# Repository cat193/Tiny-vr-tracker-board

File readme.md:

Mcu pcb is designed

IMU board is not finished yet

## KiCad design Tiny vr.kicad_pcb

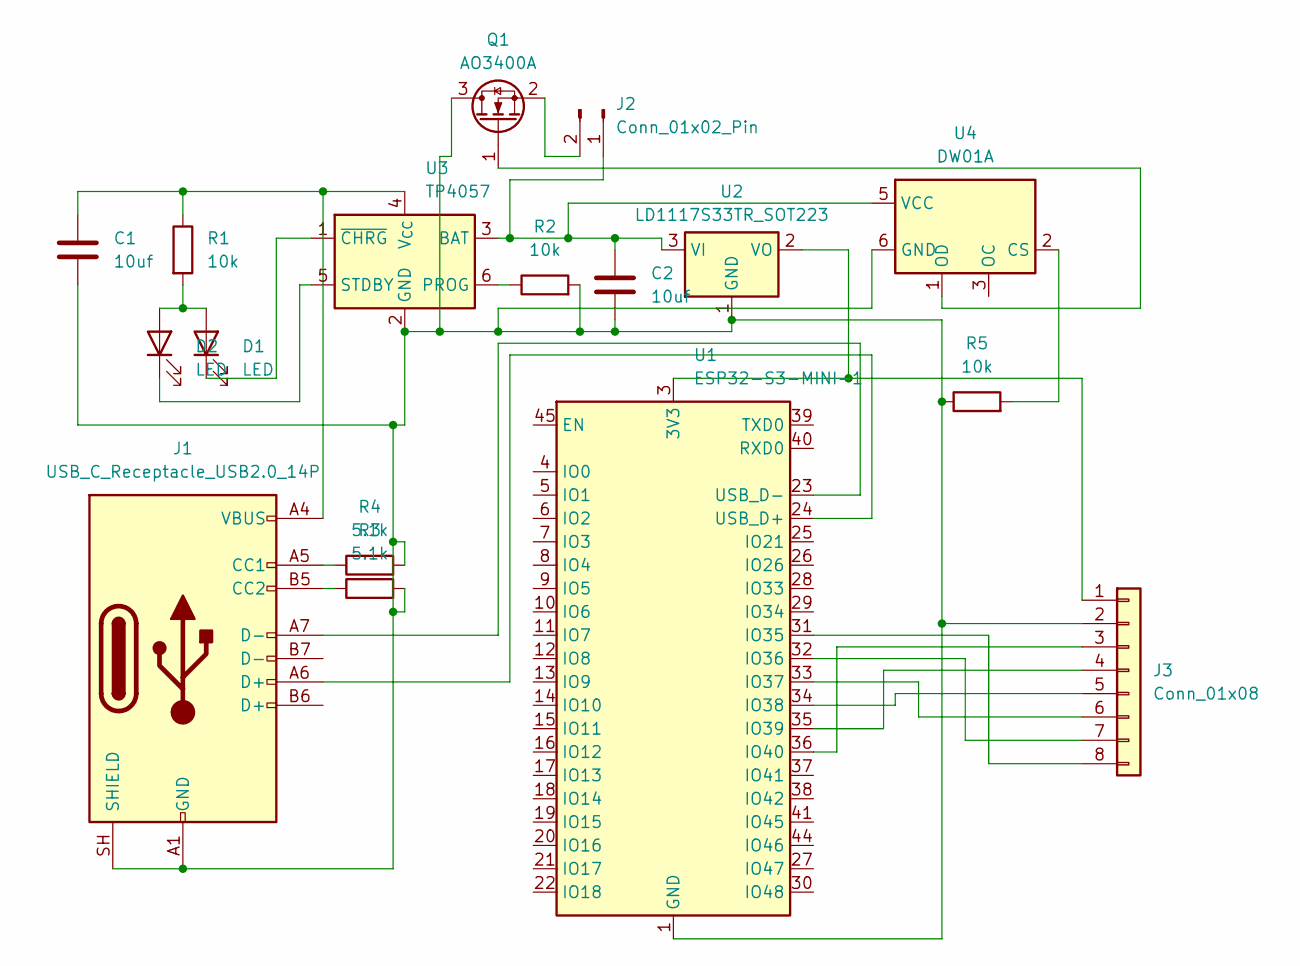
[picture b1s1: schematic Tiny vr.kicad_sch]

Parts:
C1, C2: 10uf; C_Disc_D3.0mm_W2.0mm_P2.50mm
D1, D2: LED; LED_01005_0402Metric
J1: USB_C_Receptacle_USB2.0_14P; USB_C_Receptacle_GCT_USB4105-xx-A_16P_TopMnt_Horizontal
J2: Conn_01x02_Pin; PinHeader_1x02_P2.54mm_Horizontal
J3: Conn_01x08; PinHeader_1x08_P2.54mm_Horizontal
Q1: AO3400A; SOT-23
R1, R2, R5: 10k; R_0805_2012Metric
R3, R4: 5.1k; R_0805_2012Metric
U1: ESP32-S3-MINI-1; ESP32-S2-MINI-1
U2: LD1117S33TR_SOT223; SOT-223-3_TabPin2
U3: TP4057; TSOT-23-6
U4: DW01A; SOT-23-6

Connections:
unnamed: D1.2 (A), D2.2 (A), R1.2
unnamed: D1.1 (K), U3.1 (~CHRG)
unnamed: D2.1 (K), U3.5 (STDBY)
unnamed: J1.A5 (CC1), R4.1
unnamed: J1.B5 (CC2), R3.1
unnamed: C1.2, C2.2, J1.A1 (GND), J1.A12 (GND), J1.B1 (GND), J1.B12 (GND), J1.SH (SHIELD), J3.2, Q1.3 (D), R2.2, R3.2, R4.2, R5.1, U1.1 (GND), U1.2 (GND), U1.42 (GND), U1.43 (GND), U1.46 (GND), U1.47 (GND), U1.48 (GND), U1.49 (GND), U1.50 (GND), U1.51 (GND), U1.52 (GND), U1.53 (GND), U1.54 (GND), U1.55 (GND), U1.56 (GND), U1.57 (GND), U1.58 (GND), U1.59 (GND), U1.60 (GND), U1.61 (GND), U1.62 (GND), U1.63 (GND), U1.64 (GND), U1.65 (GND), U2.1 (GND), U3.2 (GND), U4.6 (GND)
unnamed: C2.1, J2.1, U2.3 (VI), U3.3 (BAT), U4.5 (VCC)
unnamed: J2.2, Q1.2 (S)
unnamed: J3.1, U1.3 (3V3), U2.2 (VO)
unnamed: J3.3, U1.36 (IO40)
unnamed: J3.4, U1.35 (IO39)
unnamed: J3.5, U1.34 (IO38)
unnamed: J3.6, U1.33 (IO37)
unnamed: J3.7, U1.32 (IO36)
unnamed: J3.8, U1.31 (IO35)
unnamed: Q1.1 (G), U4.1 (OD)
unnamed: J1.A6 (D+), U1.24 (USB_D+)
unnamed: J1.A7 (D-), U1.23 (USB_D-)
unnamed: R2.1, U3.6 (PROG)
unnamed: C1.1, J1.A4 (VBUS), J1.A9 (VBUS), J1.B4 (VBUS), J1.B9 (VBUS), R1.1, U3.4 (V_{CC})
unnamed: R5.2, U4.2 (CS)

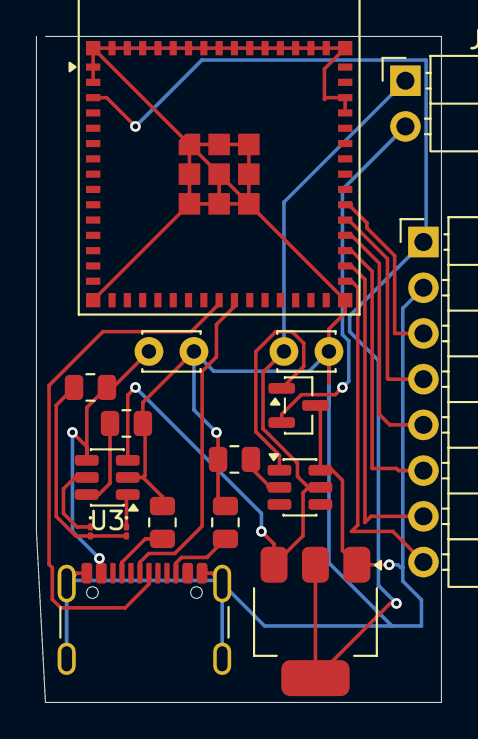
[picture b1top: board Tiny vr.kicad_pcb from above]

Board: 2 copper layers, 22.5 x 37.0 mm, 17 parts (0 on the bottom side), 21 nets.
